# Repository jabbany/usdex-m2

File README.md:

# microSD Express to M.2 2230 (Key M) adapter

A 22 x 30 mm M.2 module that holds a microSD Express card and presents it to
the host as an NVMe SSD on one PCIe Gen3 lane. It is a passive pass-through
plus a 1.8 V regulator and two AC-coupling capacitors. No bridge chip, no
firmware.

**Status: revision A0, design only. Not fabricated, not tested.** The
schematic and the routed four-layer layout agree with each other and the
layout passes KiCad's design-rule check. Before ordering boards, work through
the list in [DESIGN.md](DESIGN.md#9-open-issues-and-the-list-to-clear-before-ordering):
the differential-pair geometry is a placeholder until it is taken from your
fabricator's impedance calculator, and the socket footprint has not been
compared with the manufacturer's drawing.

Only microSD Express cards work. Ordinary microSD cards are not damaged, but a
PCIe-only host cannot see them.

## What is here

| Path | Contents |
|---|---|
| `hardware/` | KiCad 7 project: schematic, routed board, project library |
| `DESIGN.md` | the design: pin maps, rationale, footprints, layout, verification, open issues, how to change things |
| `docs/` | schematic PDF, layer images, BOM, DRC and verification reports |
| `tools/` | Python that generates the KiCad files, checks them, and exports outputs |
| `NOTICE.md` | third-party material; no licence chosen yet |

## Looking at it

Open `hardware/msdx_m2_2230.kicad_pro` in KiCad 7 or later. KiCad 8 and 9
convert the files when they save, after which KiCad 7 cannot open them.

For the 3D view of the socket, download Amphenol's STEP model as described in
`hardware/lib/3d/README.md`.

Without KiCad: `docs/schematic.pdf` and the images in `docs/img/`.

## Changing it

The KiCad files are generated from `tools/msdx/*.py`:

```
sh tools/build.sh         # regenerate and verify
sh tools/export_docs.sh   # refresh docs/
```

This needs KiCad 7 with `kicad-cli` and the `pcbnew` Python module (on Ubuntu
24.04: `apt install kicad`). You can instead edit the project directly in KiCad
and stop using the generator. Both ways are described in
[DESIGN.md, section 10](DESIGN.md#10-working-on-the-design).

## Bill of materials

One Amphenol 10102166A812A socket, one TI TLV62568DBVR buck regulator, one
2.2 uH 2016 inductor, 10 capacitors and 9 resistors (0402 and 0603), all on
the top side. Full list: [docs/bom.csv](docs/bom.csv).

## Credits

The idea and the proof that it works come from two community projects:
[vapetrov/microSD_express_Pi](https://github.com/vapetrov/microSD_express_Pi)
and [M1cha/sdexpress_pcbs](https://github.com/M1cha/sdexpress_pcbs).

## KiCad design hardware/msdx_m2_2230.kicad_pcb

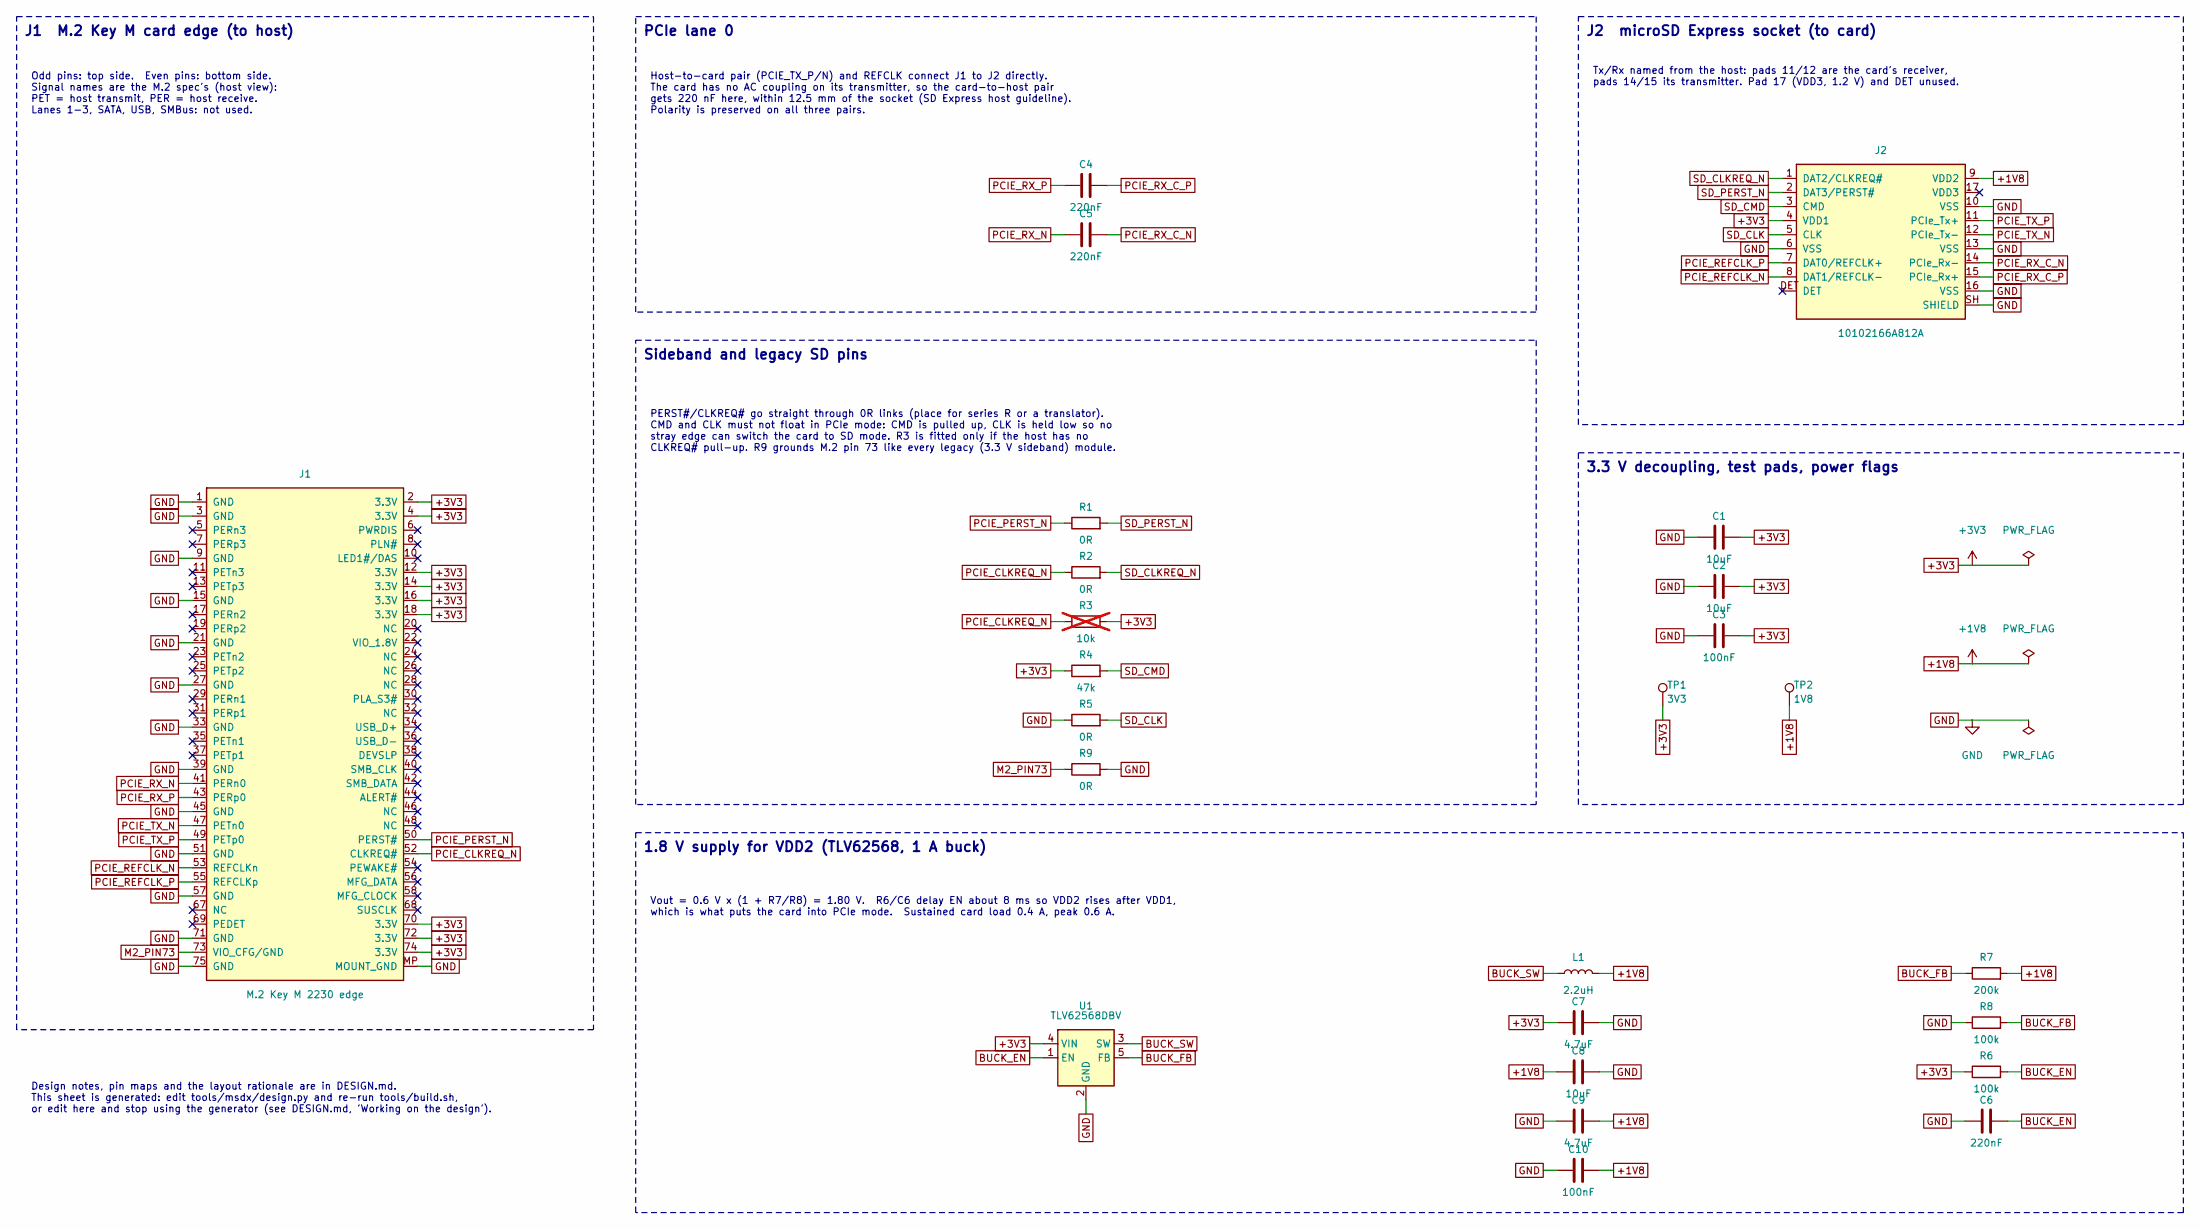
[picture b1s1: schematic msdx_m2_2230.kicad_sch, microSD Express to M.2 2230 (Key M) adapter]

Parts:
C1, C2, C8: 10uF; C_0603_1608Metric
C3, C10: 100nF; C_0402_1005Metric
C4, C5, C6: 220nF; C_0402_1005Metric
C7: 4.7uF; C_0603_1608Metric
C9: 4.7uF; C_0402_1005Metric
J1: M.2 Key M 2230 edge; M2_2230_KeyM_Edge
J2: 10102166A812A; Amphenol_10102166A812A; MPN Amphenol 10102166A812A
L1: 2.2uH; L_Murata_DFE201610P; MPN Murata DFE201612E-2R2M=P2
R1, R2, R5, R9: 0R; R_0402_1005Metric
R3: 10k; R_0402_1005Metric; not fitted
R4: 47k; R_0402_1005Metric
R6, R8: 100k; R_0402_1005Metric
R7: 200k; R_0402_1005Metric
TP1: 3V3; TestPad_D0.8mm
TP2: 1V8; TestPad_D0.8mm
U1: TLV62568DBV; SOT-23-5; MPN TI TLV62568DBVR

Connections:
+1V8: C8.1, C9.2, C10.2, J2.9 (VDD2), L1.2, R7.2, TP2.1
+3V3: C1.2, C2.2, C3.2, C7.1, J1.2 (3.3V), J1.4 (3.3V), J1.12 (3.3V), J1.14 (3.3V), J1.16 (3.3V), J1.18 (3.3V), J1.70 (3.3V), J1.72 (3.3V), J1.74 (3.3V), J2.4 (VDD1), R3.2, R4.1, R6.1, TP1.1, U1.4 (VIN)
BUCK_EN: C6.2, R6.2, U1.1 (EN)
BUCK_FB: R7.1, R8.2, U1.5 (FB)
BUCK_SW: L1.1, U1.3 (SW)
GND: C1.1, C2.1, C3.1, C6.1, C7.2, C8.2, C9.1, C10.1, J1.1 (GND), J1.3 (GND), J1.9 (GND), J1.15 (GND), J1.21 (GND), J1.27 (GND), J1.33 (GND), J1.39 (GND), J1.45 (GND), J1.51 (GND), J1.57 (GND), J1.71 (GND), J1.75 (GND), J1.MP (MOUNT_GND), J2.6 (VSS), J2.10 (VSS), J2.13 (VSS), J2.16 (VSS), J2.SH (SHIELD), R5.1, R8.1, R9.2, U1.2 (GND)
M2_PIN73: J1.73 (VIO_CFG/GND), R9.1
PCIE_CLKREQ_N: J1.52 (CLKREQ#), R2.1, R3.1
PCIE_PERST_N: J1.50 (PERST#), R1.1
PCIE_REFCLK_N: J1.53 (REFCLKn), J2.8 (DAT1/REFCLK-)
PCIE_REFCLK_P: J1.55 (REFCLKp), J2.7 (DAT0/REFCLK+)
PCIE_RX_C_N: C5.2, J2.14 (PCIe_Rx-)
PCIE_RX_C_P: C4.2, J2.15 (PCIe_Rx+)
PCIE_RX_N: C5.1, J1.41 (PERn0)
PCIE_RX_P: C4.1, J1.43 (PERp0)
PCIE_TX_N: J1.47 (PETn0), J2.12 (PCIe_Tx-)
PCIE_TX_P: J1.49 (PETp0), J2.11 (PCIe_Tx+)
SD_CLK: J2.5 (CLK), R5.2
SD_CLKREQ_N: J2.1 (DAT2/CLKREQ#), R2.2
SD_CMD: J2.3 (CMD), R4.2
SD_PERST_N: J2.2 (DAT3/PERST#), R1.2

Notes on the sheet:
J1 M.2 Key M card edge (to host)
Odd pins: top side. Even pins: bottom side. Signal names are the M.2 spec's (host view): PET = host transmit, PER = host receive. Lanes 1-3, SATA, USB, SMBus: not used.
J2 microSD Express socket (to card)
Tx/Rx named from the host: pads 11/12 are the card's receiver, pads 14/15 its transmitter. Pad 17 (VDD3, 1.2 V) and DET unused.
PCIe lane 0
Host-to-card pair (PCIE_TX_P/N) and REFCLK connect J1 to J2 directly. The card has no AC coupling on its transmitter, so the card-to-host pair gets 220 nF here, within 12.5 mm of the socket (SD Express host guideline). Polarity is preserved on all three pairs.
Sideband and legacy SD pins
PERST#/CLKREQ# go straight through 0R links (place for series R or a translator). CMD and CLK must not float in PCIe mode: CMD is pulled up, CLK is held low so no stray edge can switch the card to SD mode. R3 is fitted only if the host has no CLKREQ# pull-up. R9 grounds M.2 pin 73 like every legacy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
1.8 V supply for VDD2 (TLV62568, 1 A buck)
Vout = 0.6 V x (1 + R7/R8) = 1.80 V. R6/C6 delay EN about 8 ms so VDD2 rises after VDD1, which is what puts the card into PCIe mode. Sustained card load 0.4 A, peak 0.6 A.
3.3 V decoupling, test pads, power flags
Design notes, pin maps and the layout rationale are in DESIGN.md. This sheet is generated: edit tools/msdx/design.py and re-run tools/build.sh, or edit here and stop using the generator (see DESIGN.md, 'Working on the design').

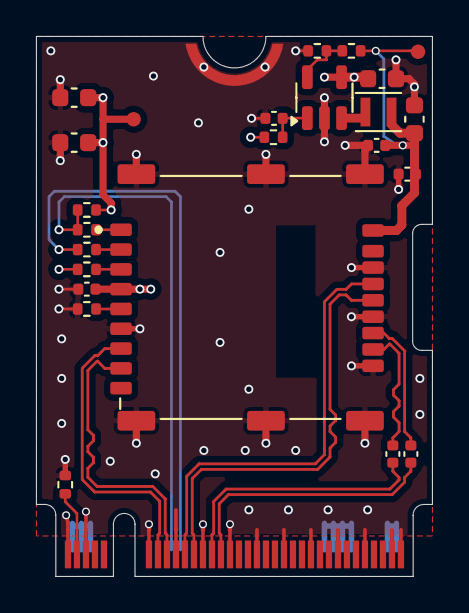
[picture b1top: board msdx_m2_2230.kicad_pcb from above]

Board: 4 copper layers, 22.0 x 30.0 mm, 25 parts (0 on the bottom side), 21 nets.

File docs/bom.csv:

Refs,Qty,Value,Footprint,Fit,MPN (suggested),Notes
C1 C2 C8,3,10uF,C_0603_1608Metric,fit,,"buck output, X5R 6.3 V; 3.3 V bulk, X5R 6.3 V; VDD1 bulk, X5R 6.3 V"
C3 C10,2,100nF,C_0402_1005Metric,fit,,"VDD2 decoupling toward socket pin 9, X7R; VDD1 decoupling at socket pin 4, X7R"
C4 C5 C6,3,220nF,C_0402_1005Metric,fit,,"EN delay; AC coupling, card Rx+ to host PERp0, X7R 10 %; AC coupling, card Rx- to host PERn0, X7R 10 %"
C7,1,4.7uF,C_0603_1608Metric,fit,,"buck input, X5R 6.3 V"
C9,1,4.7uF,C_0402_1005Metric,fit,,"buck output, second capacitor, X5R 6.3 V (0402)"
J2,1,10102166A812A,Amphenol_10102166A812A,fit,Amphenol 10102166A812A,"microSD Express socket, 3-in-1, push-pull, card detect, 1.55 mm"
L1,1,2.2uH,L_Murata_DFE201610P,fit,Murata DFE201612E-2R2M=P2,"2.2 uH, 2016, Isat >= 1.5 A, <= 1.2 mm high"
R1 R2 R5 R9,4,0R,R_0402_1005Metric,fit,,"PERST# series link (33-100 R optional); CLKREQ# series link; CLK held low (must not float; an edge selects SD mode); M.2 pin 73 (GND / VIO_CFG) to ground, legacy 3.3 V sideband module"
R3,1,10k,R_0402_1005Metric,DNP,,"CLKREQ# pull-up, fit only if the host has none"
R4,1,47k,R_0402_1005Metric,fit,,CMD pull-up (must not float in PCIe mode)
R6 R8,2,100k,R_0402_1005Metric,fit,,"feedback divider bottom, 1 %; EN pull-up; with C6 delays VDD2 about 8 ms after VDD1"
R7,1,200k,R_0402_1005Metric,fit,,"feedback divider top, 1 %"
U1,1,TLV62568DBV,SOT-23-5,fit,TI TLV62568DBVR,"1 A synchronous buck, 1.5 MHz, 0.6 V feedback"
